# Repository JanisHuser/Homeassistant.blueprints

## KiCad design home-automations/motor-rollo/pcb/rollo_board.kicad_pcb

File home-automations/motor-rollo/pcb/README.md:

# Rollo board

One board for the motor Rollo, lying on the sled in [`../rollo.scad`](../rollo.scad). It has an ESP32-H2 chip with a chip antenna, the charger, battery protection, motor driver and a 3.3 V regulator. The goal is the lowest cost at JLCPCB: every part comes from their library, Basic wherever one exists. The cell's spring-plate tab solders straight to it; the motor has two short wires to solder pads, and the cell's far end a plus lead.

**Status:** schematic in [`rollo_board.kicad_sch`](rollo_board.kicad_sch), layout in [`rollo_board.kicad_pcb`](rollo_board.kicad_pcb), fully routed. ERC and DRC are clean, with schematic parity. **Don't order it yet:** see the list at the end. Nothing built or tested on hardware. [`rollo_board.stl`](rollo_board.stl) is the board with its parts for the housings (see below).

## Size and where it sits

The board is **48.7 × 17 × 0.8 mm**, the size `rollo.scad` sets with `pcb_l` and `pcb_w` (`part="pcb_outline"` exports the outline). Its underside lies 5.4 mm above the tube's axis. Below, x runs from the antenna edge and y from the centre line, with +y the side away from the antenna (the sled's +Y).

| x (mm) | What is under the board | Parts allowed |
|---|---|---|
| 0–3.4 | Nose, outside the aluminium tube | USB-C 2 mm off-centre towards +y, sunk into a 9.24 × 6.7 mm notch in the board; antenna in the −y corner with no copper pour or vias around it |
| 3.4–44 | Coupler and motor, 0.6 mm below the board | **Top only:** at most 1.3 mm tall within ±7.5 mm, 2 mm within ±6.5 mm (the tube is higher in the middle). The USB-C stands 1.56 mm above the board and 0.8 mm below it, to x = 7.8 |
| 44–48.7 | Small bay behind the motor | Top as above. Bottom: only the motor's solder pads (J2) |

West of the ESP32-H2, R5/R6 (the 22 Ω USB resistors) sit next to the USB-C at x = 10.3, and the crystal Y1 with L1, C1 and C2 sits south-west of the chip (x ≈ 10, y −1 to −4), between the 3V3 via of pins 30/31 and the antenna line. That order (USB pins north-west, crystal south-west, antenna south) is the only one in which the chip's west pins fan out on two layers without crossings.

The status LED D2 sits on top at x = 36.2, y = +4.7 (2 × 2 mm, 0.84 mm tall), beside the red charge LED D1 at x = 34.1, y = +4.4, so one light window over that spot shows both.

The motor's rear face sits at x = 42.2. Two short wires from its tabs come through the window in the sled wall behind it into the bay and are soldered to J2's pads (M1, M2) on the board's underside at x = 45; swapping them reverses the motor, as does `ROLLO_REVERSE` in the firmware. The spring-plate tab (cell minus) lies on J3's big pad at the rear edge; the plus lead from the button plate goes to J4 beside it.

## Parts

All parts are JLCPCB/LCSC parts; the LCSC number is in each symbol's and footprint's `LCSC` field. **B** = Basic, **P** = Preferred (no setup fee either), **E** = Extended (one setup fee per part type per order).

| Block | Part | LCSC | Lib | Notes |
|---|---|---|---|---|
| MCU | ESP32-H2FH4 (QFN32) | C22470214 | E | Pinout from the datasheet v1.3, table 2-1 |
| Crystal | SX20Y032000B61T011, 32 MHz, 6 pF, 10 ppm, 2016 | C20623602 | E | 6.8 pF load caps (C1, C2), 24 nH in series on XTAL_P (L1, C74301, E) |
| RF match | 1.5 pF (C21, C22), 2.4 nH (L21) | C1552, C370211 | P, E | Start values from the Espressif guidelines; they need tuning |
| Antenna | Walsin RFECA3216060A1T, 3.1 × 1.6 × 0.6 mm | C127620 | E | $0.06 instead of $1.10 for the Johanson. R22 (0 Ω) from its second terminal to GND tunes it |
| Regulator | XC6206P332MR (SOT-23) | C5446 | B | 1 µA quiescent, 200 mA |
| Charger | TP4054 (SOT-23-5), 2.4 kΩ on PROG | C32574 | P | About 420 mA (I = 1000 V / R). Red LED (C2286, B) while charging |
| Protection | DW01A (Slkor), HJ8205 (SOT-23-6) | C42380662, C20069150 | E, P | `GND` is P−, `BATN` is the cell's minus. DW01A draws 0.7 µA |
| Motor driver | AD116 (SOT-23-6) | C7463412 | E | 1.1 A, 1.8–6 V, standby under 10 µA. $0.05 instead of $2 for the DRV8833 |
| USB-C | G-Switch GT-USB-7014C, mid-mount (sinks 1.6 mm) | C963373 | E | 5.1 kΩ on CC1/CC2, 22 Ω in D+/D−. Footprint drawn from the datasheet's recommended layout; the notch is part of the board outline |
| Button | TS-1088-AR02016, 3.9 × 3 × 2 mm | C720477 | B | BOOT (GPIO 9) |
| Status LED | Worldsemi WS2812B-2020-V6 (D2), 2 × 2 × 0.84 mm, 100 nF beside it (C20) | C52917434 | E | WS2812 protocol on GPIO 8, from 3V3. Rated 3.3–5.3 V, under 1 µA with the LEDs off, so it needs no supply switch. Its input leaves GPIO 8's pull-up working |
| Passives | 0402 resistors and capacitors, 10 µF 0603 | C25744, C25741, C26083, C25882, C11702, C25076, C25905, C25092, C17168, C1525, C52923, C1576, C19702 | B (6.8 pF and 2.4 kΩ: P) | |
| Not assembled | J2 motor pads (underside), J3/J4 cell pads | | | Bare copper, soldered by hand |

**Silkscreen:** labels at everything soldered by hand: M1/M2 on the underside, BAT+/BAT−, and BOOT. Every part's reference designator is on the top silkscreen too, for soldering by hand: 0.8 mm text where it fits, 0.6–0.7 mm in the crowded spots (C2, C11, C16, C20, R12, R15, R18, U2, U3, Y1), all with 0.15 mm strokes, and D2's inside its own outline. `production/place_silk_refs.py` placed them (run it with KiCad's Python); the minimum silk text height in the board setup is 0.6 mm for that. D2 has no silkscreen outline (it would overlap D1 and R15); its footprint is a copy of KiCad's `LED_WS2812B-2020_PLCC4_2.0x2.0mm` in `rollo_board.pretty`, whose pads match the V6 datasheet.

**3D models:** KiCad 10 ships no model for the ESP32-H2's QFN footprint, so the board uses the same-size QFN model. The antenna, the USB-C and D2 have simple block models in `rollo_board.3dshapes`: `.wrl` for the 3D viewer and `.step` boxes of the same shape for the STL export (written by hand, since KiCad's STL export only takes STEP).

**STL:** `rollo_board.stl` is the board with all parts, in mm, origin at the USB-C edge on the centre line: x along the board, +y the side away from the antenna, z = 0 the board's underside (top at 0.8). The USB-C reaches z = −0.8 and 2.36. Re-export it after changing the layout:

```bash
/Applications/KiCad/KiCad.app/Contents/MacOS/kicad-cli pcb export stl --subst-models --user-origin 100x100mm -f -o rollo_board.stl rollo_board.kicad_pcb
```

**Setup fees:** 9 Extended part types (ESP32-H2, crystal, antenna, two inductors, DW01A, AD116, USB-C, status LED). Every other part is Basic or Preferred.

## Charging

The USB-C faces the wall through an opening in the sled's nose. When the blind is hung, the bracket is 1 mm from the nose, so no plug fits. To charge, lift the blind out of its brackets and pull the key with its hex rod out of the nose, then plug in. The sled stays in the tube.

## Pins

| GPIO | Net | |
|---|---|---|
| 10, 11 | AD116 AIN, BIN | As AIN1/AIN2 in `firmware/main/board.h`. 100 kΩ pull-downs keep the motor off during boot. Both low: off, both high: brake |
| 1 | Battery level | ADC1_CH0. The firmware doesn't read it yet |
| 9 | BOOT button | Strapping pin, 10 kΩ pull-up |
| 8 | Status LED D2 (WS2812) | Strapping pin with a 10 kΩ pull-up; high is needed for download mode. The LED's input draws under 1 µA, so the pull-up still wins |
| 26, 27 | USB D−, D+ | |
| 0, 4, 23, 24 | Free | The AD116 has no sleep or fault pin. The firmware's sleep pin (GPIO 4) now drives nothing, which is harmless |

## Open before ordering

- **Keep the solder joints low.** The bay under J2 is 2.6 mm deep, and the cell pads on top have to stay within 1.3 mm of the board.
- **No reset or serial pads.** Flash and read logs over the USB-C. If the firmware ever disables USB, hold BOOT while connecting the battery to get into download mode.
- **The radio is the biggest risk.** The antenna's datasheet wants an 8 × 3 mm empty area at the board edge; here it gets about 4 × 4 mm, about 2.3 mm from the USB-C's shell legs, with only 3.4 mm of board outside the tube. Tune C21/L21/C22 and R22, or at least check the range, before building it in.
- **The AD116 has no current limit.** The DRV8833's 1 A limit is gone, and the AD116 only has thermal protection. The firmware runs the motor by time, so a stall at the end stop lasts until the timer runs out.
- **The XC6206 gives 200 mA.** That covers the H2 (its radio peaks well below that), but it is half what Espressif's generic guideline asks for. If the H2 browns out while transmitting, use a bigger LDO.
- **Check the USB-C footprint** against the GT-USB-7014C drawing (pad row 6.7–7.8 mm from the edge, legs at ±5.62 mm, 2.1 and 6.1 mm from the edge, notch 9.24 × 6.7 mm). The notch's inner corners come out rounded from the router (about 0.5 mm); the body clears that.
- **Check the pinouts against the datasheets** of the parts you get: TP4054 (1 CHRG, 2 GND, 3 BAT, 4 VCC, 5 PROG), HJ8205 (1 S1, 2 D, 3 S2, 4 G2, 5 D, 6 G1), AD116 (1 BOUT, 2 GND, 3 BIN, 4 AIN, 5 VCC, 6 AOUT), the crystal (pins 1 and 3 the crystal, 2 and 4 ground) and the antenna (pad 1 feed).
- **Review the routing in KiCad.** Hand-routed and locked: the USB-C fanout and D+/D− pair (D− crosses under D+ through two vias), CC1/CC2, VBUS, the west side of the ESP32-H2 with the crystal, the antenna line, and the motor outputs AO1/AO2, which run along the bottom and top edges on B.Cu so they don't cut the ground plane through the protection circuit. Freerouting 2.2.4 routed the rest; 12 extra vias stitch the top ground pour to the bottom plane. The bottom plane is still cut by several power traces, so check the ground return around U2/U3/Q1.
- **The crystal is close to the antenna line.** XTAL_P runs about 0.9 mm from the ANT trace between U1 and C21. Check the RF match and the crystal's frequency on the first boards.
- **Supply voltage:** the H2 wants 3.0–3.6 V. Below about 3.3 V on the cell the LDO's output drops under that, so the firmware should stop the motor and sleep before then.
- **Firmware:** read the battery level on GPIO 1. The status LED stays on GPIO 8 as on the Super Mini.
- **D2 at 3.3 V is at the bottom of its range.** The WS2812B-2020-V6 is rated from 3.3 V; the XC6206 gives 3.3 V ± 2 %, and less when the cell drops below about 3.4 V. Check it lights correctly at the lowest cell voltage the firmware allows.
- **Production files** for ordering the board and building it by hand are in [`production/`](production): Gerbers with the stencil layer, an LCSC parts list and a placement plan. Order it as 2 layers, 0.8 mm thick, smallest trace 0.15 mm, smallest hole 0.3 mm.

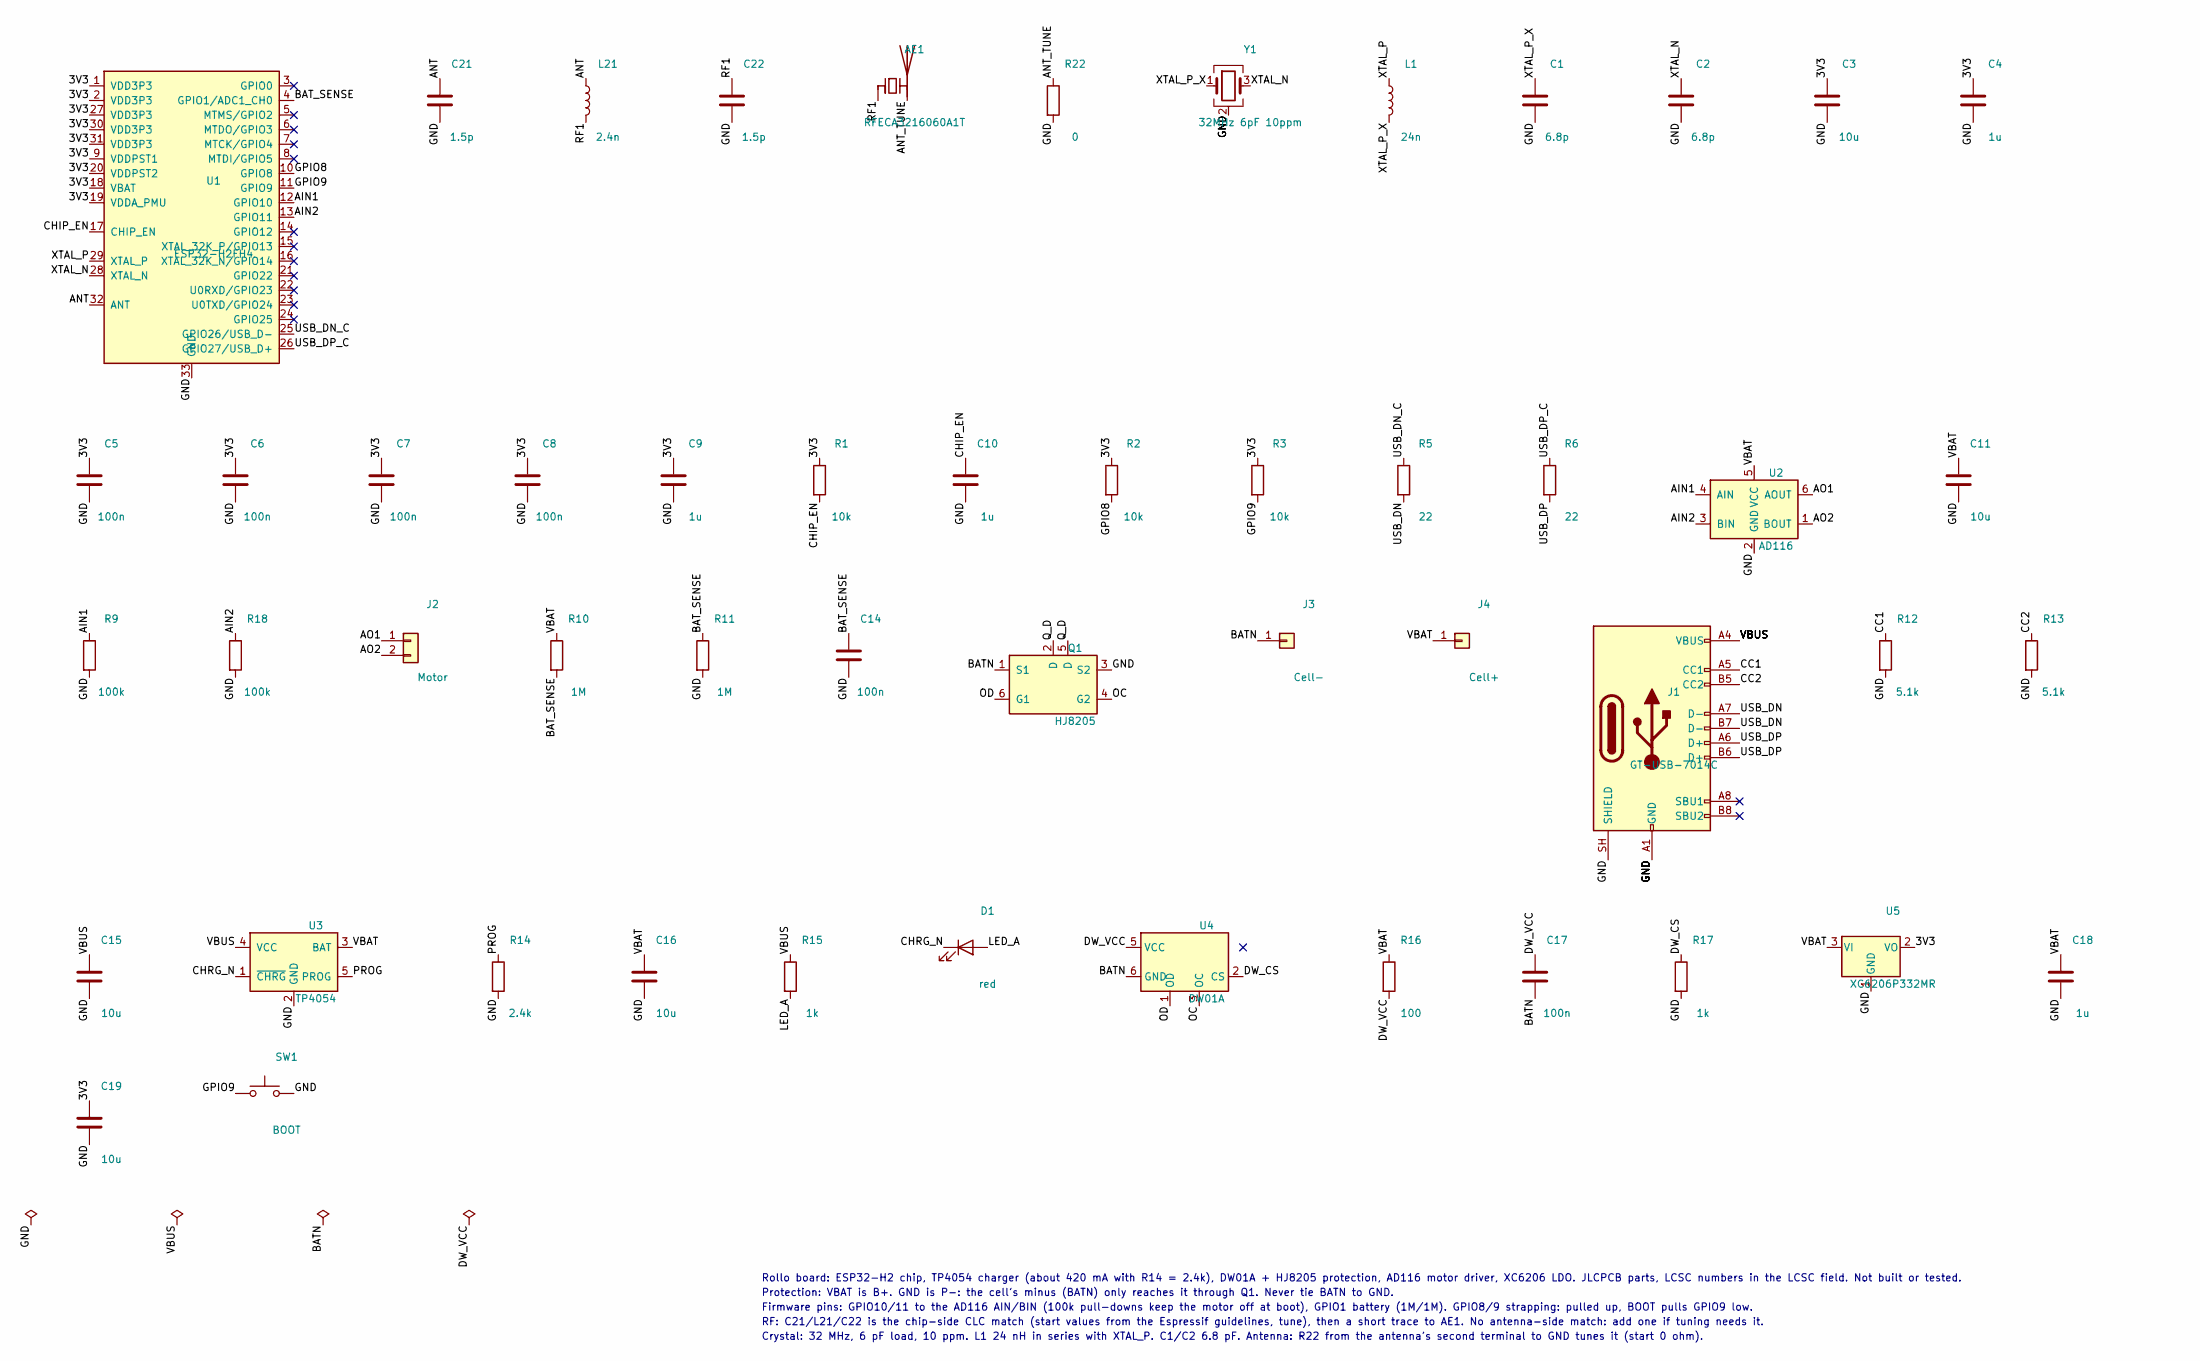
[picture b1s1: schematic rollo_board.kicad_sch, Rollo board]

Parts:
AE1: RFECA3216060A1T; Walsin_RFECA3216; LCSC C127620
C1, C2: 6.8p; C_0402_1005Metric; LCSC C1576
C3, C11, C15, C16, C19: 10u; C_0603_1608Metric; LCSC C19702
C4, C9, C10, C18: 1u; C_0402_1005Metric; LCSC C52923
C5, C6, C7, C8, C14, C17: 100n; C_0402_1005Metric; LCSC C1525
C21, C22: 1.5p; C_0402_1005Metric; LCSC C1552
D1: red; LED_0603_1608Metric; LCSC C2286
J1: GT-USB-7014C; USB_C_GSwitch_GT-USB-7014C; LCSC C963373
J2: Motor; MotorPads
J3: Cell-; CellTab
J4: Cell+; WirePad
L1: 24n; L_0402_1005Metric; LCSC C74301
L21: 2.4n; L_0402_1005Metric; LCSC C370211
Q1: HJ8205; SOT-23-6; LCSC C20069150
R1, R2, R3: 10k; R_0402_1005Metric; LCSC C25744
R5, R6: 22; R_0402_1005Metric; LCSC C25092
R9, R18: 100k; R_0402_1005Metric; LCSC C25741
R10, R11: 1M; R_0402_1005Metric; LCSC C26083
R12, R13: 5.1k; R_0402_1005Metric; LCSC C25905
R14: 2.4k; R_0402_1005Metric; LCSC C25882
R15, R17: 1k; R_0402_1005Metric; LCSC C11702
R16: 100; R_0402_1005Metric; LCSC C25076
R22: 0; R_0402_1005Metric; LCSC C17168
SW1: BOOT; SW_SPST_TS-1088-xR020; LCSC C720477
U1: ESP32-H2FH4; VQFN-32-1EP_4x4mm_P0.4mm_EP2.8x2.8mm; LCSC C22470214
U2: AD116; SOT-23-6; LCSC C7463412
U3: TP4054; SOT-23-5; LCSC C32574
U4: DW01A; SOT-23-6; LCSC C42380662
U5: XC6206P332MR; SOT-23; LCSC C5446
Y1: 32MHz 6pF 10ppm; Crystal_SMD_2016-4Pin_2.0x1.6mm; LCSC C20623602

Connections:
/3V3: C3.1, C4.1, C5.1, C6.1, C7.1, C8.1, C9.1, C19.1, R1.1, R2.1, R3.1, U1.1 (VDD3P3), U1.2 (VDD3P3), U1.9 (VDDPST1), U1.18 (VBAT), U1.19 (VDDA_PMU), U1.20 (VDDPST2), U1.27 (VDD3P3), U1.30 (VDD3P3), U1.31 (VDD3P3), U5.2 (VO); also elsewhere on the board
/AIN1: R9.1, U1.12 (GPIO10), U2.4 (AIN)
/AIN2: R18.1, U1.13 (GPIO11), U2.3 (BIN)
/ANT: C21.1, L21.1, U1.32 (ANT)
/ANT_TUNE: AE1.2 (PCB_Trace), R22.1
/AO1: J2.1, U2.6 (AOUT)
/AO2: J2.2, U2.1 (BOUT)
/BATN: C17.2, J3.1, Q1.1 (S1), U4.6 (GND)
/BAT_SENSE: C14.1, R10.2, R11.1, U1.4 (GPIO1/ADC1_CH0)
/CC1: J1.A5 (CC1), R12.1
/CC2: J1.B5 (CC2), R13.1
/CHIP_EN: C10.1, R1.2, U1.17 (CHIP_EN)
/CHRG_N: D1.1 (K), U3.1 (~CHRG)
/DW_CS: R17.1, U4.2 (CS)
/DW_VCC: C17.1, R16.2, U4.5 (VCC)
/GND: C1.2, C2.2, C3.2, C4.2, C5.2, C6.2, C7.2, C8.2, C9.2, C10.2, C11.2, C14.2, C15.2, C16.2, C18.2, C19.2, C21.2, C22.2, J1.A1 (GND), J1.A12 (GND), J1.B1 (GND), J1.B12 (GND), J1.SH (SHIELD), Q1.3 (S2), R9.2, R11.2, R12.2, R13.2, R14.2, R17.2, R18.2, R22.2, SW1.2, U1.33 (GND), U2.2 (GND), U3.2 (GND), U5.1 (GND), Y1.2 (G), Y1.4 (G); also elsewhere on the board
/GPIO8: R2.2, U1.10 (GPIO8); also elsewhere on the board
/GPIO9: R3.2, SW1.1, U1.11 (GPIO9)
/LED_A: D1.2 (A), R15.2
/OC: Q1.4 (G2), U4.3 (OC)
/OD: Q1.6 (G1), U4.1 (OD)
/PROG: R14.1, U3.5 (PROG)
/Q_D: Q1.2 (D), Q1.5 (D)
/RF1: AE1.1 (FEED), C22.1, L21.2
/USB_DN: J1.A7 (D-), J1.B7 (D-), R5.2
/USB_DN_C: R5.1, U1.25 (GPIO26/USB_D-)
/USB_DP: J1.A6 (D+), J1.B6 (D+), R6.2
/USB_DP_C: R6.1, U1.26 (GPIO27/USB_D+)
/VBAT: C11.1, C16.1, C18.1, J4.1, R10.1, R16.1, U2.5 (VCC), U3.3 (BAT), U5.3 (VI)
/VBUS: C15.1, J1.A4 (VBUS), J1.A9 (VBUS), J1.B4 (VBUS), J1.B9 (VBUS), R15.1, U3.4 (VCC)
/XTAL_N: C2.1, U1.28 (XTAL_N), Y1.3
/XTAL_P: L1.1, U1.29 (XTAL_P)
/XTAL_P_X: C1.1, L1.2, Y1.1

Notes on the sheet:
Rollo board: ESP32-H2 chip, TP4054 charger (about 420 mA with R14 = 2.4k), DW01A + HJ8205 protection, AD116 motor driver, XC6206 LDO. JLCPCB parts, LCSC numbers in the LCSC field. Not built or tested.
Protection: VBAT is B+. GND is P-: the cell's minus (BATN) only reaches it through Q1. Never tie BATN to GND.
Firmware pins: GPIO10/11 to the AD116 AIN/BIN (100k pull-downs keep the motor off at boot), GPIO1 battery (1M/1M). GPIO8/9 strapping: pulled up, BOOT pulls GPIO9 low.
RF: C21/L21/C22 is the chip-side CLC match (start values from the Espressif guidelines, tune), then a short trace to AE1. No antenna-side match: add one if tuning needs it.
Crystal: 32 MHz, 6 pF load, 10 ppm. L1 24 nH in series with XTAL_P. C1/C2 6.8 pF. Antenna: R22 from the antenna's second terminal to GND tunes it (start 0 ohm).

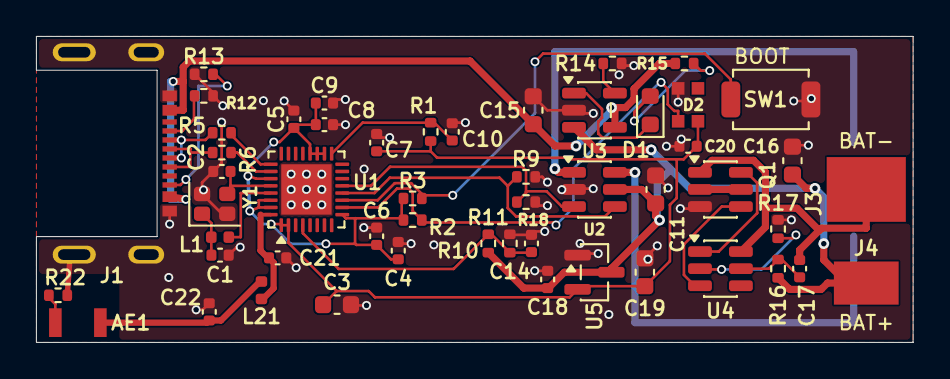
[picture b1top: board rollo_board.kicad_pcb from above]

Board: 2 copper layers, 48.7 x 17.0 mm, 53 parts (1 on the bottom side), 33 nets.

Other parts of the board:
C20: 100n; C_0402_1005Metric
D2: WS2812B-2020-V6; LED_WS2812B-2020

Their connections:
/3V3: C20.1, D2.4; also elsewhere on the board
/GND: C20.2, D2.2; also elsewhere on the board
/GPIO8: D2.3; also elsewhere on the board

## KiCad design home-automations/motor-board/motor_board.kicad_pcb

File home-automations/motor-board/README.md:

# Motor board

One carrier board for the battery-powered motor projects: the [DIY valve head](../diy-valve-head) and the [motor Rollo](../motor-rollo). An ESP32-H2 Super Mini solders flat onto it. The charger, battery protection and motor driver are parts on the board.

**Status:** schematic in [`motor_board.kicad_sch`](motor_board.kicad_sch), layout in [`motor_board.kicad_pcb`](motor_board.kicad_pcb), autorouted with Freerouting. **Don't order it yet:** see the list at the end. Nothing built or tested on hardware.

## What is on it

| Block | Parts | Notes |
|---|---|---|
| Charger | TP4056, 2.4 kΩ on PROG | 500 mA, to stay cool in a closed housing |
| Protection | DW01A, FS8205A | In the cell's minus lead. `GND` is P−, `BATN` is the cell's minus |
| Driver | DRV8833 | Channel A only. R7 (0.2 Ω) limits the motor to about 1 A; fit 0 Ω for no limit |
| Battery level | 2 × 1 MΩ, 100 nF | On GPIO 1, as in the valve head firmware |
| Encoder | AO3401A, pull-ups | Rollo only. The FET cuts the encoder's power during sleep |

## Pins

| GPIO | Net | Used by |
|---|---|---|
| 1 | Battery level | Both |
| 10, 11 | DRV8833 AIN1, AIN2 | Both |
| 4 | DRV8833 sleep | Both |
| 0 | DRV8833 fault | Both (firmware does not read it yet) |
| 5 | Encoder power, low = on | Rollo |
| 12, 14 | Encoder A, B | Rollo |

GPIO 2, 3, 8, 9 and 25 are strapping pins, and GPIO 8 and 13 drive the Super Mini's LEDs, so nothing on this board uses them. GPIO 14 is free only because the firmware doesn't use an external 32 kHz crystal.

## Wire pads

| Ref | Goes to | Used by |
|---|---|---|
| J1 | USB-C snap socket, VBUS and GND (the socket needs its own CC resistors) | Both |
| J2 | 18650 contact plates | Both |
| J3 | Motor | Both |
| J4 | Encoder: power, GND, A, B | Rollo |

## Fitting by project

| | Valve head | Rollo |
|---|---|---|
| Leave off | Q2, R9, R10, R11, J4 | Nothing |
| Battery wires | Short, battery is right under the board | Through the journal (Ø9 mm) |
| Motor wires | Short | Through the journal, with the encoder's four |

## Size

The board is **21 × 27.6 mm**. The Super Mini sits on top and everything else on the underside, with the wire pads in one row at the USB end. The Super Mini's antenna end hangs 3 mm past the board, so no copper or board sits under it, and its USB-C end stays over the board. That makes 30.6 mm in all.

| Project | How it sits | What it took |
|---|---|---|
| Valve head | Pressed into a pocket over the battery, wire pads towards the drive | Tray 37.5 mm deep |
| Rollo | Slides into two rails in the head, antenna towards the wall, Super Mini facing down so BOOT and RESET are reachable through two pin holes | Head Ø30 and longer for its screw-in lid, so the tube is 777 mm and the fabric 773 mm at most. The cartridge is 133 mm |

The stack is 1.7 mm underside parts, 0.8 mm board, 0.1 mm solder, 1.2 mm Super Mini and 3.3 mm its USB-C.

## Footprint

`motor_board.pretty/ESP32H2-Supermini` comes from [esp32-h2-supermini-kicad](https://github.com/Zektopic/esp32-h2-supermini-kicad) (MIT, licence file next to it). Changed here: unused pads removed (GPIO 8, 9, 22, 25, 26, 27), stray drawing lines from its template removed, and a new outline and courtyard for a 24 × 18.4 mm board.

Edge clearance is set to 0.3 mm, and the board has ground planes on both sides and three thermal vias each under U1 and U2.

Its edge pads are drilled, and B+/B− have 1.5 mm holes, so you can solder those two through the board. Its pad rows are 15.34 mm apart and differ from each other by 0.03 mm along the board, which looks hand-placed, so check them against a real board before ordering.

## Production files

In [`production/`](production): `motor_board_gerber.zip` (Gerbers and drill file), `motor_board_BOM.csv`, and position files for assembly, one per project.

Order it as: 2 layers, 21 × 27.6 mm, **0.8 mm thick**, 1 oz copper. Smallest trace 0.15 mm, smallest hole 0.3 mm. All parts except the Super Mini are on the underside. Export them again after any change to the board.

## Open before ordering

- Review the autorouted traces in KiCad. Power and motor traces are 0.3 mm (0.23 mm near pads) and signals 0.2 mm, narrowing to 0.15 mm at fine-pitch pads. The design check flags those 0.15 mm parts against the 0.2 mm rule; check your manufacturer can make them.
- Measure the Super Mini: outline, edge pad positions, B+/B− pads, and where its antenna sits. Print the footprint at 1:1 and lay the board on it.
- Check that B+/B− suit a battery feed. The Super Mini's own charger stays connected to them, so its USB-C must not be plugged in while the battery is connected.
- Check the FS8205A pinout against the datasheet of the part you buy.
- Test the motors: the 1 A limit in R7 may be too low for the valve's closing force.
- The Rollo has no firmware yet.

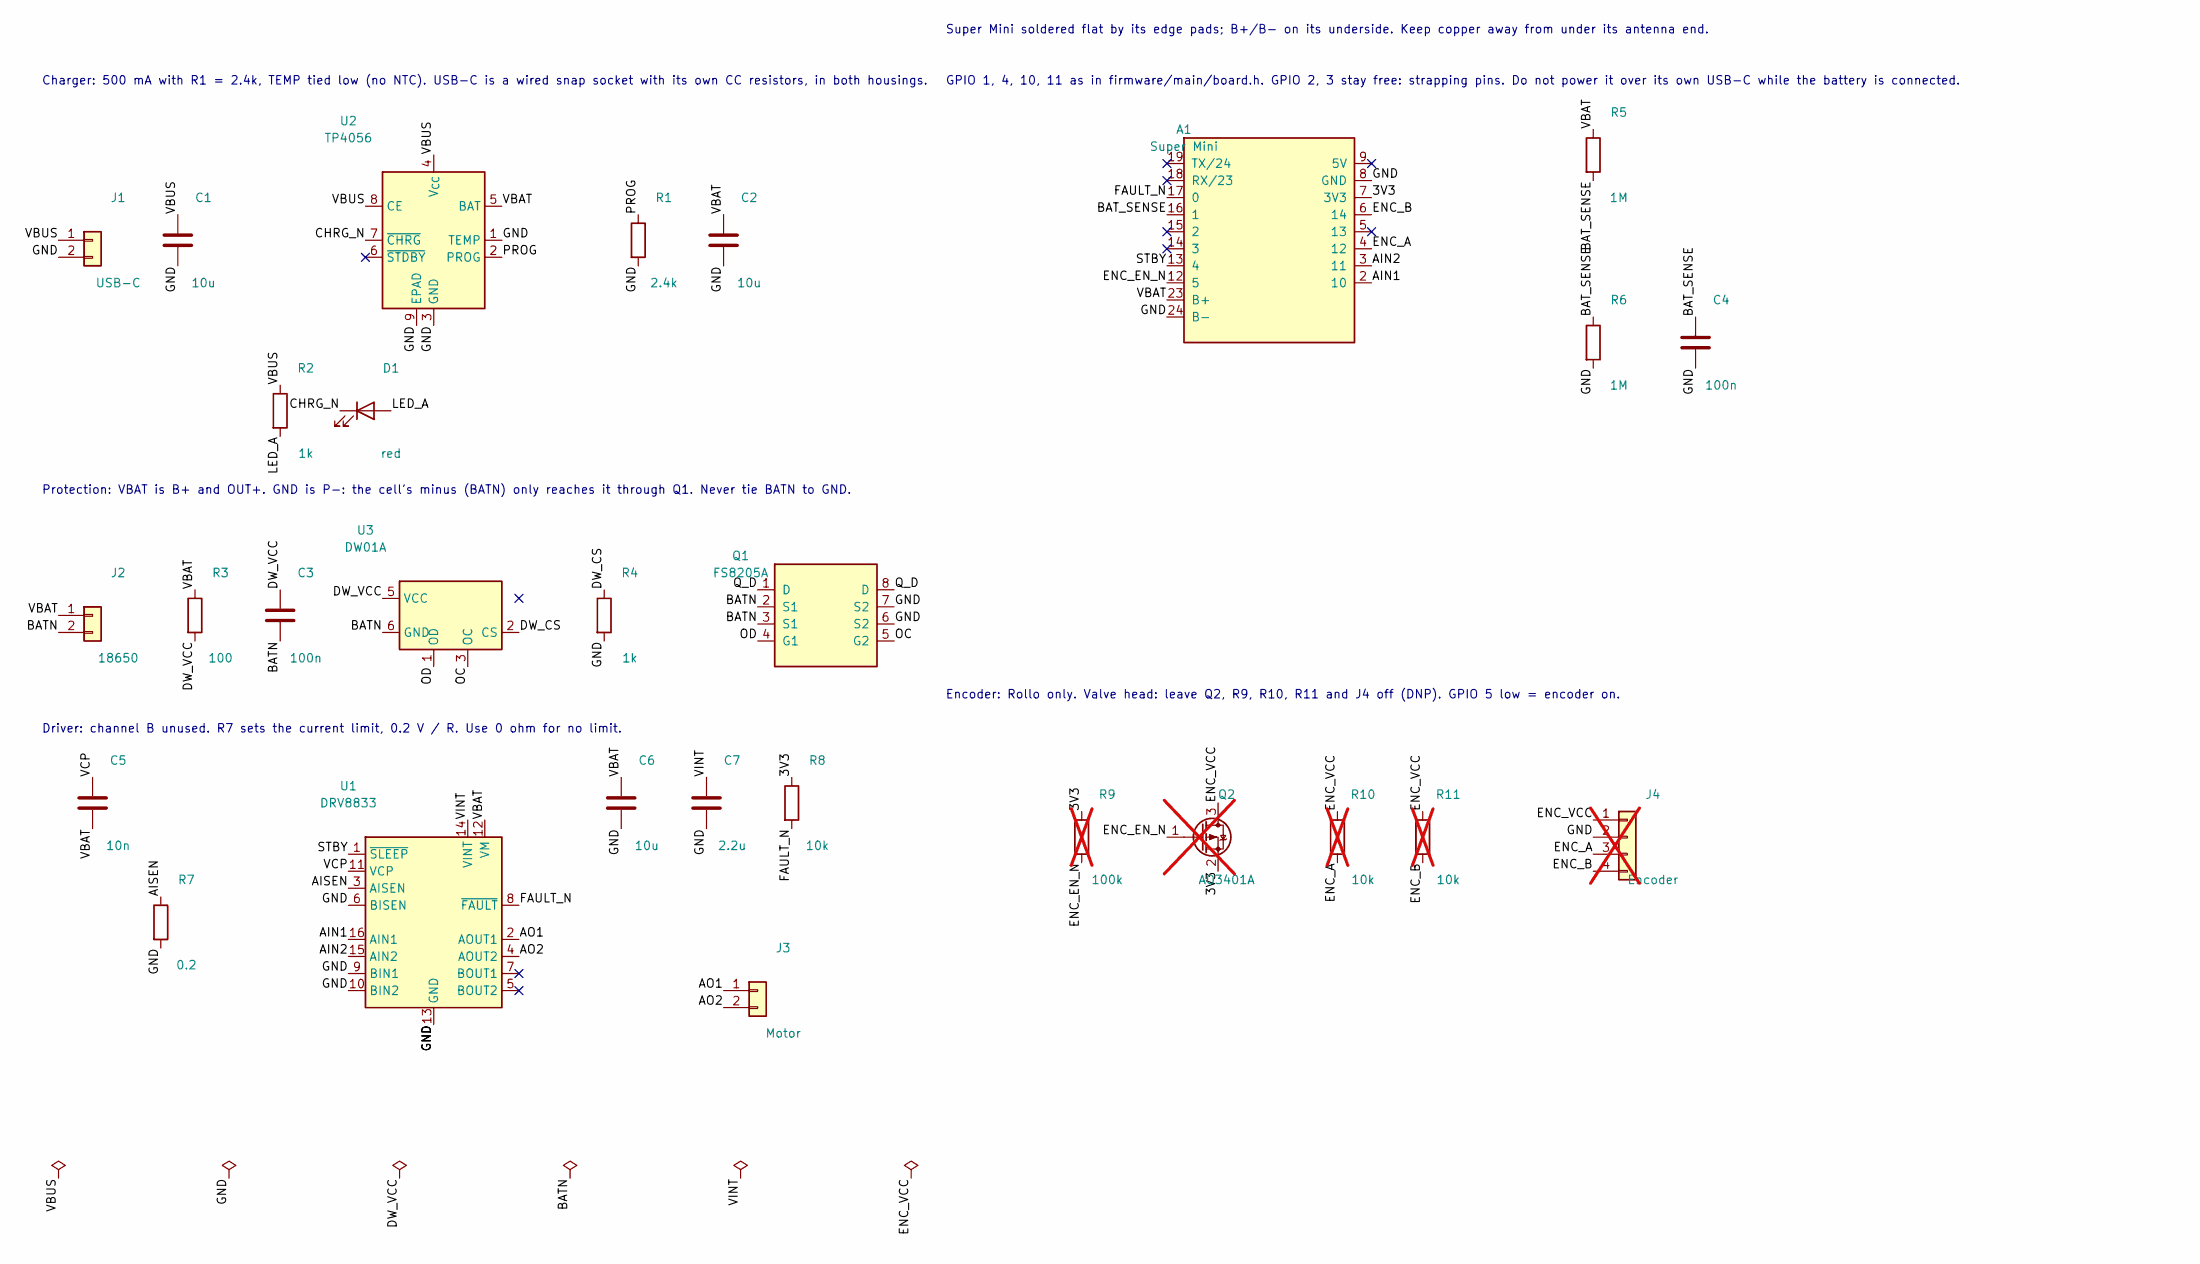
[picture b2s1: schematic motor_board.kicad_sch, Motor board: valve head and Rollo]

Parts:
A1: Super Mini; ESP32H2-Supermini
C1, C2, C6: 10u; C_0603_1608Metric
C3, C4: 100n; C_0603_1608Metric
C5: 10n; C_0603_1608Metric
C7: 2.2u; C_0603_1608Metric
D1: red; LED_0603_1608Metric
J1: USB-C; WirePads_1x02_P2.00mm
J2: 18650; WirePads_1x02_P2.00mm
J3: Motor; WirePads_1x02_P2.00mm
J4: Encoder; WirePads_1x04_P2.00mm; not fitted
Q1: FS8205A; TSSOP-8_4.4x3mm_P0.65mm
Q2: AO3401A; SOT-23; not fitted
R1: 2.4k; R_0603_1608Metric
R2, R4: 1k; R_0603_1608Metric
R3: 100; R_0603_1608Metric
R5, R6: 1M; R_0603_1608Metric
R7: 0.2; R_1206_3216Metric
R8: 10k; R_0603_1608Metric
R9: 100k; R_0603_1608Metric; not fitted
R10, R11: 10k; R_0603_1608Metric; not fitted
U1: DRV8833; HTSSOP-16-1EP_4.4x5mm_P0.65mm_EP3.4x5mm_Mask2.46x2.31mm
U2: TP4056; SOIC-8-1EP_3.9x4.9mm_P1.27mm_EP2.41x3.3mm
U3: DW01A; SOT-23-6

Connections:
/3V3: A1.7 (3V3), Q2.2 (S), R8.1, R9.1
/AIN1: A1.2 (10), U1.16 (AIN1)
/AIN2: A1.3 (11), U1.15 (AIN2)
/AISEN: R7.1, U1.3 (AISEN)
/AO1: J3.1, U1.2 (AOUT1)
/AO2: J3.2, U1.4 (AOUT2)
/BATN: C3.2, J2.2, Q1.2 (S1), Q1.3 (S1), U3.6 (GND)
/BAT_SENSE: A1.16 (1), C4.1, R5.2, R6.1
/CHRG_N: D1.1 (K), U2.7 (~CHRG)
/DW_CS: R4.1, U3.2 (CS)
/DW_VCC: C3.1, R3.2, U3.5 (VCC)
/ENC_A: A1.4 (12), J4.3, R10.2
/ENC_B: A1.6 (14), J4.4, R11.2
/ENC_EN_N: A1.12 (5), Q2.1 (G), R9.2
/ENC_VCC: J4.1, Q2.3 (D), R10.1, R11.1
/FAULT_N: A1.17 (0), R8.2, U1.8 (~FAULT)
/GND: A1.8 (GND), A1.24 (B-), C1.2, C2.2, C4.2, C6.2, C7.2, J1.2, J4.2, Q1.6 (S2), Q1.7 (S2), R1.2, R4.2, R6.2, R7.2, U1.6 (BISEN), U1.9 (BIN1), U1.10 (BIN2), U1.13 (GND), U1.17 (GND), U2.1 (TEMP), U2.3 (GND), U2.9 (EPAD)
/LED_A: D1.2 (A), R2.2
/OC: Q1.5 (G2), U3.3 (OC)
/OD: Q1.4 (G1), U3.1 (OD)
/PROG: R1.1, U2.2 (PROG)
/Q_D: Q1.1 (D), Q1.8 (D)
/STBY: A1.13 (4), U1.1 (~SLEEP)
/VBAT: A1.23 (B+), C2.1, C5.2, C6.1, J2.1, R3.1, R5.1, U1.12 (VM), U2.5 (BAT)
/VBUS: C1.1, J1.1, R2.1, U2.4 (V_{CC}), U2.8 (CE)
/VCP: C5.1, U1.11 (VCP)
/VINT: C7.1, U1.14 (VINT)

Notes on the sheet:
Charger: 500 mA with R1 = 2.4k, TEMP tied low (no NTC). USB-C is a wired snap socket with its own CC resistors, in both housings.
Protection: VBAT is B+ and OUT+. GND is P-: the cell's minus (BATN) only reaches it through Q1. Never tie BATN to GND.
Super Mini soldered flat by its edge pads; B+/B- on its underside. Keep copper away from under its antenna end.
GPIO 1, 4, 10, 11 as in firmware/main/board.h. GPIO 2, 3 stay free: strapping pins. Do not power it over its own USB-C while the battery is connected.
Driver: channel B unused. R7 sets the current limit, 0.2 V / R. Use 0 ohm for no limit.
Encoder: Rollo only. Valve head: leave Q2, R9, R10, R11 and J4 off (DNP). GPIO 5 low = encoder on.

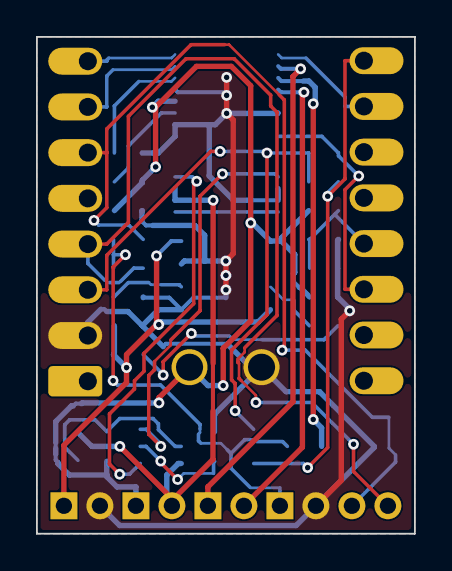
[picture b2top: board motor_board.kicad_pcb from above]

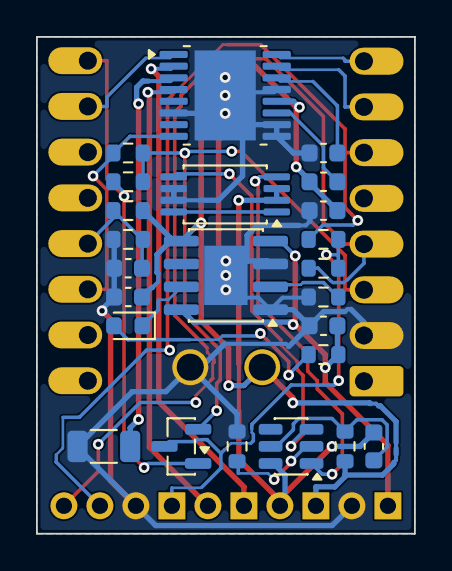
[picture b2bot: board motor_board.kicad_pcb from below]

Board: 2 copper layers, 21.0 x 27.6 mm, 29 parts (28 on the bottom side), 27 nets.

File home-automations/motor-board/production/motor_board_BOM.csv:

Ref,Qty valve head,Qty Rollo,Value,Part,Description,Footprint
A1,1,1,Super Mini,ESP32-H2 Super Mini,"Dev board, buy separately, hand-solder on top",ESP32H2-Supermini
C1 C2 C6,3,3,10u,,"Capacitor, 10 uF, X5R, 10 V or more, 0603",C_0603_1608Metric
C3 C4,2,2,100n,,"Capacitor, 100 nF, X7R, 16 V or more, 0603",C_0603_1608Metric
C5,1,1,10n,,"Capacitor, 10 nF, X7R, 16 V or more, 0603 (VCP)",C_0603_1608Metric
C7,1,1,2.2u,,"Capacitor, 2.2 uF, X5R, 10 V or more, 0603 (VINT)",C_0603_1608Metric
D1,1,1,red,,"LED, red, 0603",LED_0603_1608Metric
J1,1,1,USB-C,,"Wire pads to the USB-C socket, no part",WirePads_1x02_P2.00mm
J2,1,1,18650,,"Wire pads to the 18650 holder, no part",WirePads_1x02_P2.00mm
J3,1,1,Motor,,"Wire pads to the motor, no part",WirePads_1x02_P2.00mm
J4,0,1,Encoder,,"Wire pads to the encoder, no part",WirePads_1x04_P2.00mm
Q1,1,1,FS8205A,FS8205A,"Dual N-MOSFET, TSSOP-8; check its pinout against the datasheet",TSSOP-8_4.4x3mm_P0.65mm
Q2,0,1,AO3401A,AO3401A,"P-MOSFET, SOT-23",SOT-23
R1,1,1,2.4k,,"Resistor, 2.4k ohm, 1%, 0603",R_0603_1608Metric
R2 R4,2,2,1k,,"Resistor, 1k ohm, 1%, 0603",R_0603_1608Metric
R3,1,1,100,,"Resistor, 100 ohm, 1%, 0603",R_0603_1608Metric
R5 R6,2,2,1M,,"Resistor, 1M ohm, 1%, 0603",R_0603_1608Metric
R7,1,1,0.2,,"Current sense, 0.2 ohm, 1%, 0.25 W or more, 1206",R_1206_3216Metric
R8,1,1,10k,,"Resistor, 10k ohm, 1%, 0603",R_0603_1608Metric
R9,0,1,100k,,"Resistor, 100k ohm, 1%, 0603",R_0603_1608Metric
R10 R11,0,2,10k,,"Resistor, 10k ohm, 1%, 0603",R_0603_1608Metric
U1,1,1,DRV8833,DRV8833PWPR,"Motor driver, TI, HTSSOP-16 with thermal pad",HTSSOP-16-1EP_4.4x5mm_P0.65mm_EP3.4x5mm_Mask2.46x2.31mm
U2,1,1,TP4056,TP4056,"Li-ion charger, ESOP-8 with thermal pad",SOIC-8-1EP_3.9x4.9mm_P1.27mm_EP2.41x3.3mm
U3,1,1,DW01A,DW01A,"Battery protection IC, SOT-23-6",SOT-23-6

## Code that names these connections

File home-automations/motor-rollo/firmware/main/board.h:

/* Pins of the Rollo (ESP32-H2 Super Mini with a DRV8833 board) and the motor driver.
   The motor pins are set in menuconfig (main/Kconfig.projbuild). */
#pragma once

#include <cstdint>

#include <hal/gpio_types.h>
#include <sdkconfig.h>

#include "units.h"

#if !CONFIG_IDF_TARGET_ESP32H2
#error "The Rollo runs on the ESP32-H2 Super Mini"
#endif

#define PIN_MOTOR_IN1   static_cast<gpio_num_t>(CONFIG_ROLLO_PIN_IN1)    // -> DRV8833 AIN1
#define PIN_MOTOR_IN2   static_cast<gpio_num_t>(CONFIG_ROLLO_PIN_IN2)    // -> DRV8833 AIN2
#define PIN_MOTOR_SLEEP static_cast<gpio_num_t>(CONFIG_ROLLO_PIN_SLEEP)  // -> DRV8833 STBY (high = on)
#define PIN_RGB_LED     GPIO_NUM_8   // WS2812 status LED: the Super Mini's, or D2 on the rollo board (main/led.cpp)
#define PIN_BUTTON      GPIO_NUM_9   // BOOT button

constexpr uint32_t GPIO_LEVEL_LOW = 0;
constexpr uint32_t GPIO_LEVEL_HIGH = 1;
constexpr uint32_t BUTTON_PRESSED_LEVEL = GPIO_LEVEL_LOW;

/* The argument esp_pm_lock_create() takes is unused for ESP_PM_NO_LIGHT_SLEEP. */
constexpr int PM_LOCK_NO_ARG = 0;

enum class motor_dir_t { up, down };

void board_init();
/* Wakes the driver and runs the motor until board_motor_stop(). Keeps the chip out of light sleep meanwhile.
   reversed swaps the direction (on top of ROLLO_REVERSE). */
void board_motor_start(motor_dir_t dir, bool reversed);
/* Brakes, then sleeps the driver. */
void board_motor_stop();
